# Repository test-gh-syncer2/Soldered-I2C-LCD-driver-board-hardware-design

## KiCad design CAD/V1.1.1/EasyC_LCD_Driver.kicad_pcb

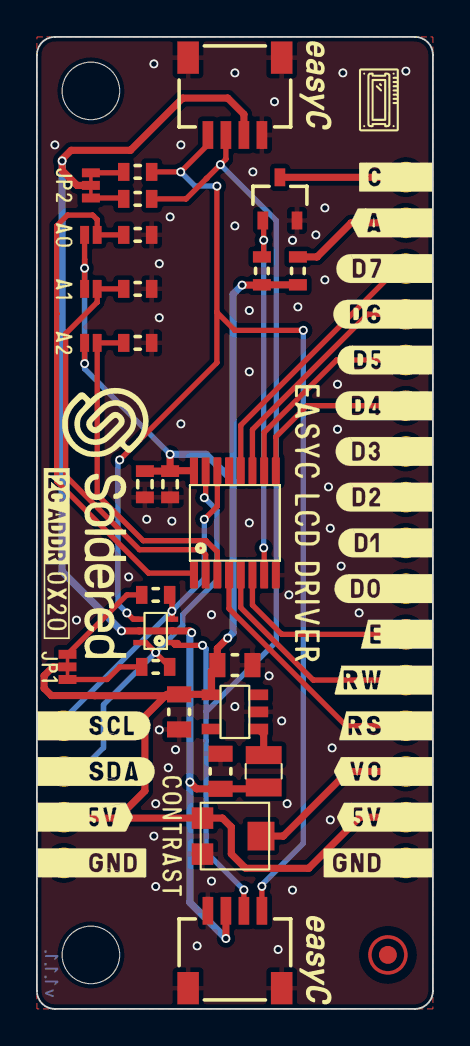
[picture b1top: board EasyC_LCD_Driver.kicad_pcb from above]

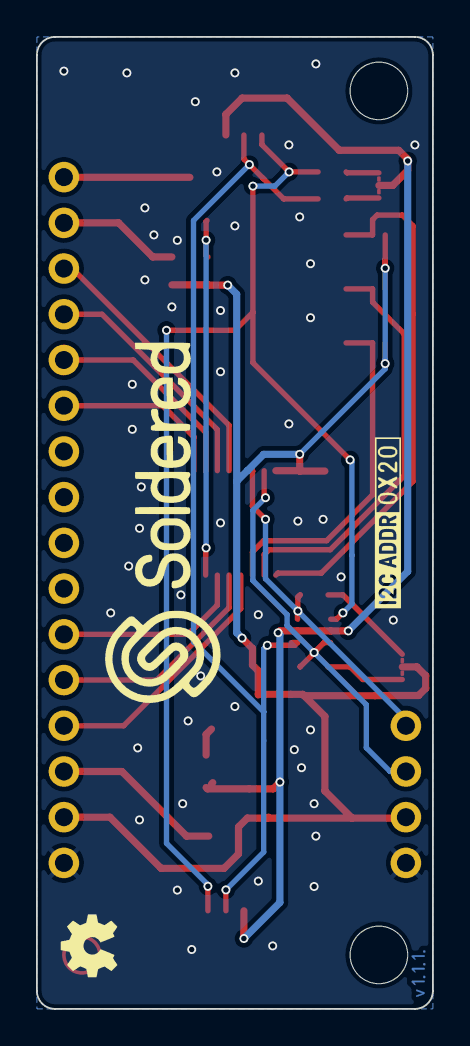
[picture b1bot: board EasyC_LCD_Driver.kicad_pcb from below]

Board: 2 copper layers, 22.0 x 54.0 mm, 33 parts (2 on the bottom side), 26 nets.

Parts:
C1, C2: CL10A226MPCNUBE; 0805C
C3: 1uF; 0603C
C4: 0.1uF; 0603C
C5: C1608X7S1A475K080AC; 0805C
FD1: FIDUCIAL; FIDUCIAL_23
H1, H2: HOLE_3.2mm
JP1, JP2, JP3: SMD_JUMPER
JP4, JP5: SMD_JUMPER_3_PAD_TRACE
K1, K2: easyC-SMD; easyC-connector
K3, K4: HEADER_MALE_8X1
K5: HEADER_MALE_4X1
L1: DFE201612E-2R2M=P2; 0806L
Q1: NMOS-SOT-23-3; SOT-23-3
R1, R2, R3: 100k; 0603R
R4, R6, R8, R9, R10: 10k; 0603R
R5: 330R; 0603R
R7: tc33x-2-103e
U1: TCA9534PWR; TSSOP-16
U2: TPS613222A; tps613222a
U3: NMOS-DUAL; SOT-363

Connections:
3V3: C5.2, JP5.2, K1.3 (3V3), K2.3 (3V3), L1.2, U3.2 (G2), U3.5 (G1)
5V: C1.2, C2.2, C3.1, C4.1, JP1.2, JP2.2, JP3.2, JP4.2, K4.2, K5.2, R4.1, R5.1, R7.1, U1.16 (VCC), U2.4 (VOUT)
A0: JP1.1, R1.2, U1.1 (A0)
A1: JP2.1, R2.2, U1.2 (A1)
A2: JP3.1, R3.2, U1.3 (A2)
C: K3.8, Q1.3 (D)
GND: C1.1, C2.1, C3.2, C4.2, C5.1, K1.4 (GND), K1.5 (SHIELD), K2.4 (GND), K2.5 (SHIELD), K4.1, K5.1, Q1.2 (S), R1.1, R2.1, R3.1, R7.3, U1.8 (GND), U2.2 (GND)
unnamed: K3.7, R5.2
unnamed: K4.3, R7.2
unnamed: L1.1, U2.1 (SW)
P0: K4.4, U1.4 (P0)
P1: K4.5, U1.5 (P1)
P2: K4.6, U1.6 (P2)
P3: Q1.1 (G), R4.2, U1.7 (P3)
P4: K3.3, U1.9 (P4)
P5: K3.4, U1.10 (P5)
P6: K3.5, U1.11 (P6)
P7: K3.6, U1.12 (P7)
SCL: K1.1 (SCL), K2.1 (SCL), R10.1, U3.4 (S1)
SCL5: K5.4, R8.2, U1.14 (SCL), U3.3 (D1)
SCL_PULL3,3: JP5.1, R10.2
SCL_PULL5: JP4.1, R8.1
SDA: K1.2 (SDA), K2.2 (SDA), R6.2, U3.1 (S2)
SDA5: K5.3, R9.1, U1.15 (SDA), U3.6 (D2)
SDA_PULL3,3: JP5.3, R6.1
SDA_PULL5: JP4.3, R9.2

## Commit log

2021-09-23 Syncing to git
2021-09-23 Updating open source files.
